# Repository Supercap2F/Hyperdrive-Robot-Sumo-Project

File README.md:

# Hyperdrive-Robot-Sumo-Project
Open Source Robot Sumo Project

* Start Date: Friday, November 28, 2014
*  End Date: ---
*   Version: 1.0

# About
The project started out on November 28th, 2014 - But under a different name: "Epsilon - The Universal Robot".
After more work was done, it was changed to "Hyperdrive!", named after my one of my favorite songs from the band
Guardian. The robot's main function is for Robot sumo, but will also have programs that will allow it to also
be a line flowing robot, and more.

#### Note: You can find photos of the robot in: Hyperdrive-Robot-Sumo-Project/Images/Robot Photos

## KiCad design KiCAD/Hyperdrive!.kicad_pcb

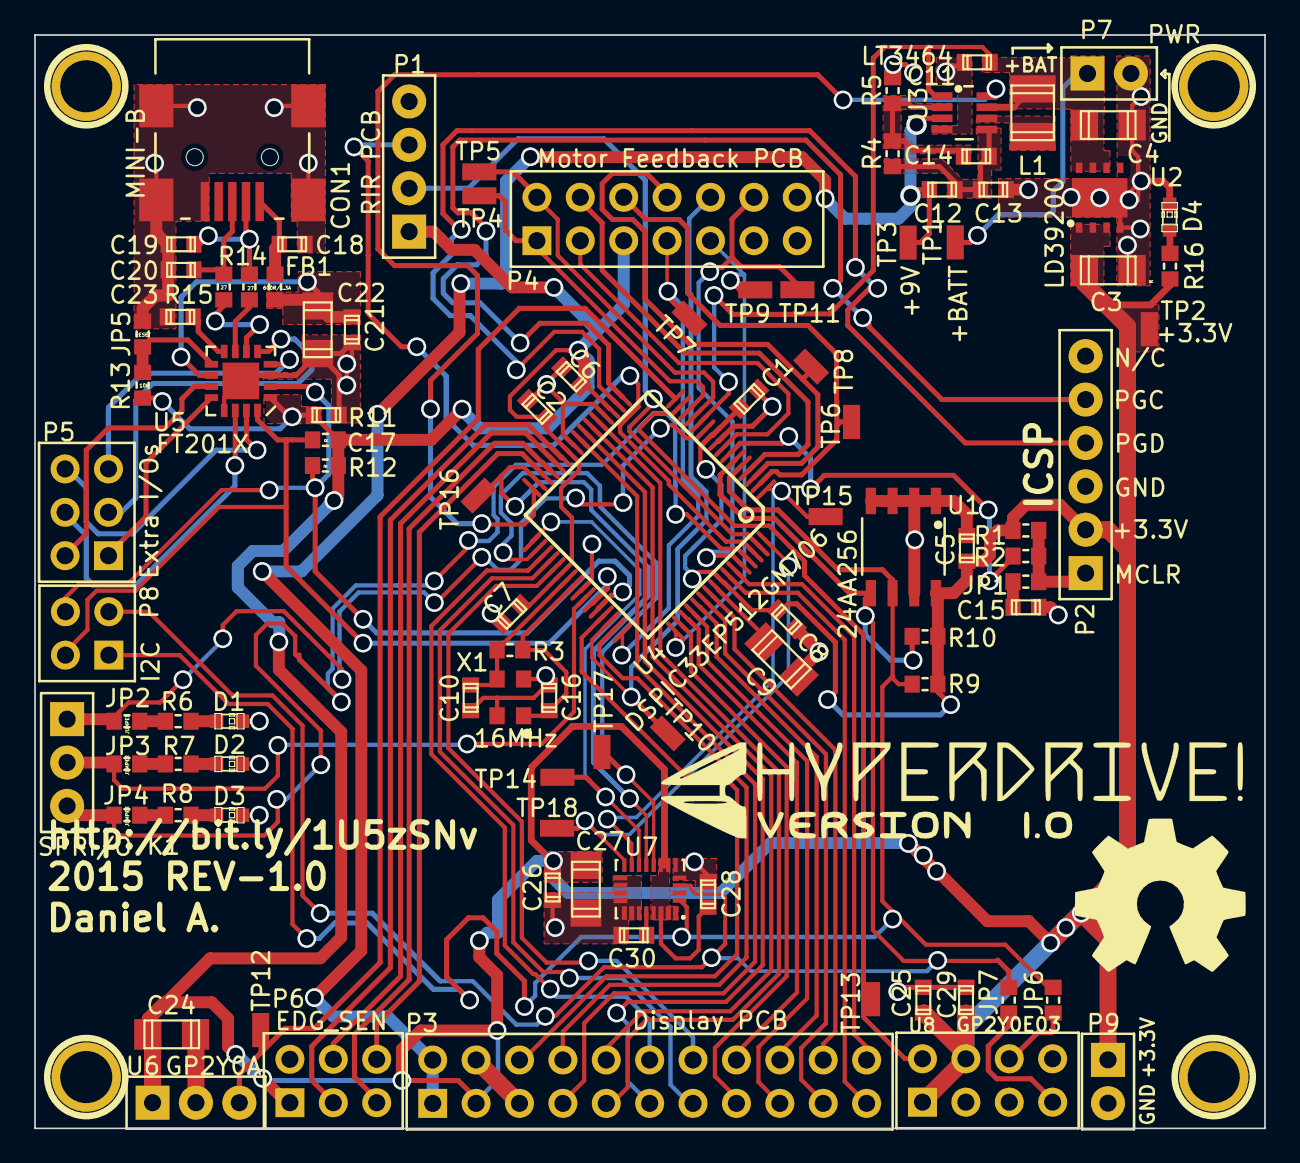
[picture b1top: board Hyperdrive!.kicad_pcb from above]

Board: 2 copper layers, 72.0 x 64.0 mm, 98 parts (0 on the bottom side), 87 nets.

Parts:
C1, C2, C6, C7, C8, C15: 0.1u; c_0603
C3, C4: 10uF; c_1206
C5, C17, C18, C21, C23, C25, C26, C28, C29: 100n; c_0603
C9, C24, C27: 10u; c_1206
C10, C14, C16: 20p; c_0603
C11: 1u; c_0603
C12: 0.47u; c_0603
C13: 2.2u; c_0603
C19, C20: 47p; c_0603
C22: 4.7u; c_1206
C30: 10n; c_0603
CON1: Mini_B
D1, D2, D3, D4: LED-0603
FB1: 600R/1.3A; r_0603
JP1: MCLR; r_0603
JP2, JP3, JP4: JUMPER; r_0603
JP5: RESET; r_0603
JP6: SCL; r_0603
JP7: SDA; r_0603
K1: CON_3x1
L1: 47u; c_1210
P1: CON_4x1
P2: CON_6x1
P3: CON_11x2
P4: CON_7x2
P5, P6: CON_3x2
P7: PWR; CON_2x1
P8: CON_2x2
P9: CON_2x1
R1, R13: 10K; r_0603
R2: 100; r_0603
R3: 1M; r_0603
R4: 1908K; r_0603
R5: 300K; r_0603
R6, R7, R8: 220; r_0603
R9, R10, R11, R12, R16: R; r_0603
R14, R15: 27; r_0603
TP1, TP2, TP3, TP4, TP5, TP6, TP7, TP8, TP9, TP10, TP11, TP12, TP13, TP14, TP15, TP16, TP17, TP18: TP
U1: 24AA256; SOIC_8
U2: LD39200; DFN8
U3: LT3464; TSOT-23
U4: DSPIC33EP512GM706; TQFP_64
U5: FT201X; QFN-16
U6: CON_3x1
U7: LGA-24
U8: CON_4x2
VAL: REF; Hyperdrive!_F.SilkS_40mm
X1: 16MHz; Crystal_2.5x3.2

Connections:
+3.3V: C1.2, C2.1, C3.1, C5.1, C6.2, C7.1, C8.1, C17.1, C24.1, C25.1, C26.1, C27.1, C28.1, C29.1, P1.1, P2.2, P3.3, P4.5, P6.1, P9.1, R1.2, R9.1, R10.1, R11.1, R12.1, R13.1, R16.1, TP2.1, U1.8, U2.1, U2.2, U2.3, U4.10, U4.19, U4.26, U4.38, U4.57, U5.1, U6.1, U7.1, U7.3, U7.7, U7.8, U7.22, U7.23, U7.24, U8.1, U8.4
+9V: C12.1, P3.1, P3.2, TP3.1, U3.3
+BATT: C4.1, C11.1, L1.2, P7.1, TP1.1, U2.6, U2.7, U2.8, U3.1, U3.7, U4.12
/CS#: P3.17, U4.52
/D0: P3.9, U4.21
/D1: P3.10, U4.22
/D2: P3.11, U4.23
/D3: P3.12, U4.35
/D4: P3.13, U4.36
/D5: P3.14, U4.37
/D6: P3.15, U4.50
/D7: P3.16, U4.51
/D/C#: P3.6, U4.45
/DIRL: P4.7, TP7.1, U4.48
/DIRR: P4.10, TP10.1, U4.46
/E/RD#: P3.8, U4.47
/FAULTL: P4.12, TP11.1, U4.60
/FAULTR: P4.9, TP9.1, U4.49
/I/03: JP4.2, K1.3, U4.61
/I/O1: JP2.2, K1.1, U4.11
/I/O2: JP3.2, K1.2, U4.42
/IRBDS: P1.2, U4.63
/IRPWM: P1.3, U4.62
/MCLR: JP1.2, P2.1, R1.1, R2.1
/MSL: P4.1, TP4.1, U4.14
/MSR: P4.2, TP5.1, U4.13
/PGC: P2.5, U4.17
/PGD: P2.4, U4.18
/PWML: P4.8, TP8.1, U4.3
/PWMR: P4.6, TP6.1, U4.2
/R/W#: P3.7, U4.24
/RES#: P3.20, U4.55
/SCL/FM+: P8.3, R11.2, U4.43, U5.16
/SDA/FM+: P8.4, R12.2, U4.44, U5.2
/SHDN: U3.8, U4.32
/ST1: P3.21, U4.58
/ST2: P3.22, U4.59
/ST3: P3.19, U4.54
/ST4: P3.18, U4.53
/Sensors /AD1: P6.3, U4.27
/Sensors /AD2: P6.4, U4.28
/Sensors /AD3: P6.5, U4.29
/Sensors /AD4: P6.6, U4.30
/Sensors /IMU_DEN_G: TP18.1, U4.64, U7.13
/Sensors /IMU_INT1_A: TP14.1, U4.33, U7.11
/Sensors /IMU_INT1_G: TP16.1, U4.31, U7.10
/Sensors /IMU_INT2_A: TP15.1, U4.1, U7.12
/Sensors /IMU_INT2_G: TP17.1, U4.34, U7.9
/Sensors /IMU_SCL: JP6.2, P8.1, R9.2, U1.6, U4.5, U7.2
/Sensors /IMU_SDA: JP7.2, P8.2, R10.2, U1.5, U4.6, U7.4
/Sensors /IRDS_VO: TP12.1, U4.16, U6.3
/Sensors /IRLDS_VO: TP13.1, U4.15, U8.2
/VBUS: C21.1, C22.1, FB1.2, U5.10
/VDD: P4.3, U4.8
/VDD2: P4.4, U4.4
GND: C1.1, C2.2, C3.2, C4.2, C5.2, C6.1, C7.2, C8.2, C9.2, C10.2, C11.2, C13.2, C15.2, C16.2, C17.2, C18.2, C19.2, C20.2, C21.2, C22.2, C23.2, C24.2, C25.2, C26.2, C27.2, C28.2, C29.2, C30.2, CON1.5, CON1.6, CON1.7, CON1.8, CON1.9, D1.2, D2.2, D3.2, D4.2, JP5.2, P1.4, P2.3, P3.4, P3.5, P4.11, P4.13, P4.14, P6.2, P7.2, P9.2, R5.2, U1.1, U1.2, U1.3, U1.4, U1.7, U2.4, U2.9, U3.4, U4.9, U4.20, U4.25, U4.41, U5.3, U5.13, U5.17, U6.2, U7.5, U7.6, U7.14, U7.15, U7.16, U7.17, U7.18, U7.19, U7.20, U8.3, X1.3, X1.4
unnamed: C18.1, CON1.1, FB1.1
unnamed: C19.1, CON1.2, R14.1
unnamed: C20.1, CON1.3, R15.1
unnamed: C15.1, JP1.1
unnamed: JP5.1, R13.2, U5.9
unnamed: C9.1, U4.56
unnamed: C23.1, U5.8
unnamed: R14.2, U5.7
unnamed: R15.2, U5.6
unnamed: JP3.1, R7.1
unnamed: JP4.1, R8.1
unnamed: P5.1, U5.12
unnamed: P5.2, U5.11
unnamed: P5.3, U5.5
unnamed: P5.4, U5.14
unnamed: P5.5, U5.4
unnamed: P5.6, U5.15
unnamed: D1.1, R6.2
unnamed: D2.1, R7.2
unnamed: D3.1, R8.2
unnamed: JP2.1, R6.1
unnamed: R2.2, U4.7
unnamed: C16.1, R3.2, U4.40, X1.1
unnamed: C10.1, R3.1, U4.39, X1.2
unnamed: D4.1, R16.2
unnamed: C12.2, C13.1, C14.1, R4.1, U3.5
unnamed: C14.2, R4.2, R5.1, U3.2
unnamed: L1.1, U3.6
unnamed: JP6.1, U8.6
unnamed: JP7.1, U8.7
unnamed: C30.1, U7.21

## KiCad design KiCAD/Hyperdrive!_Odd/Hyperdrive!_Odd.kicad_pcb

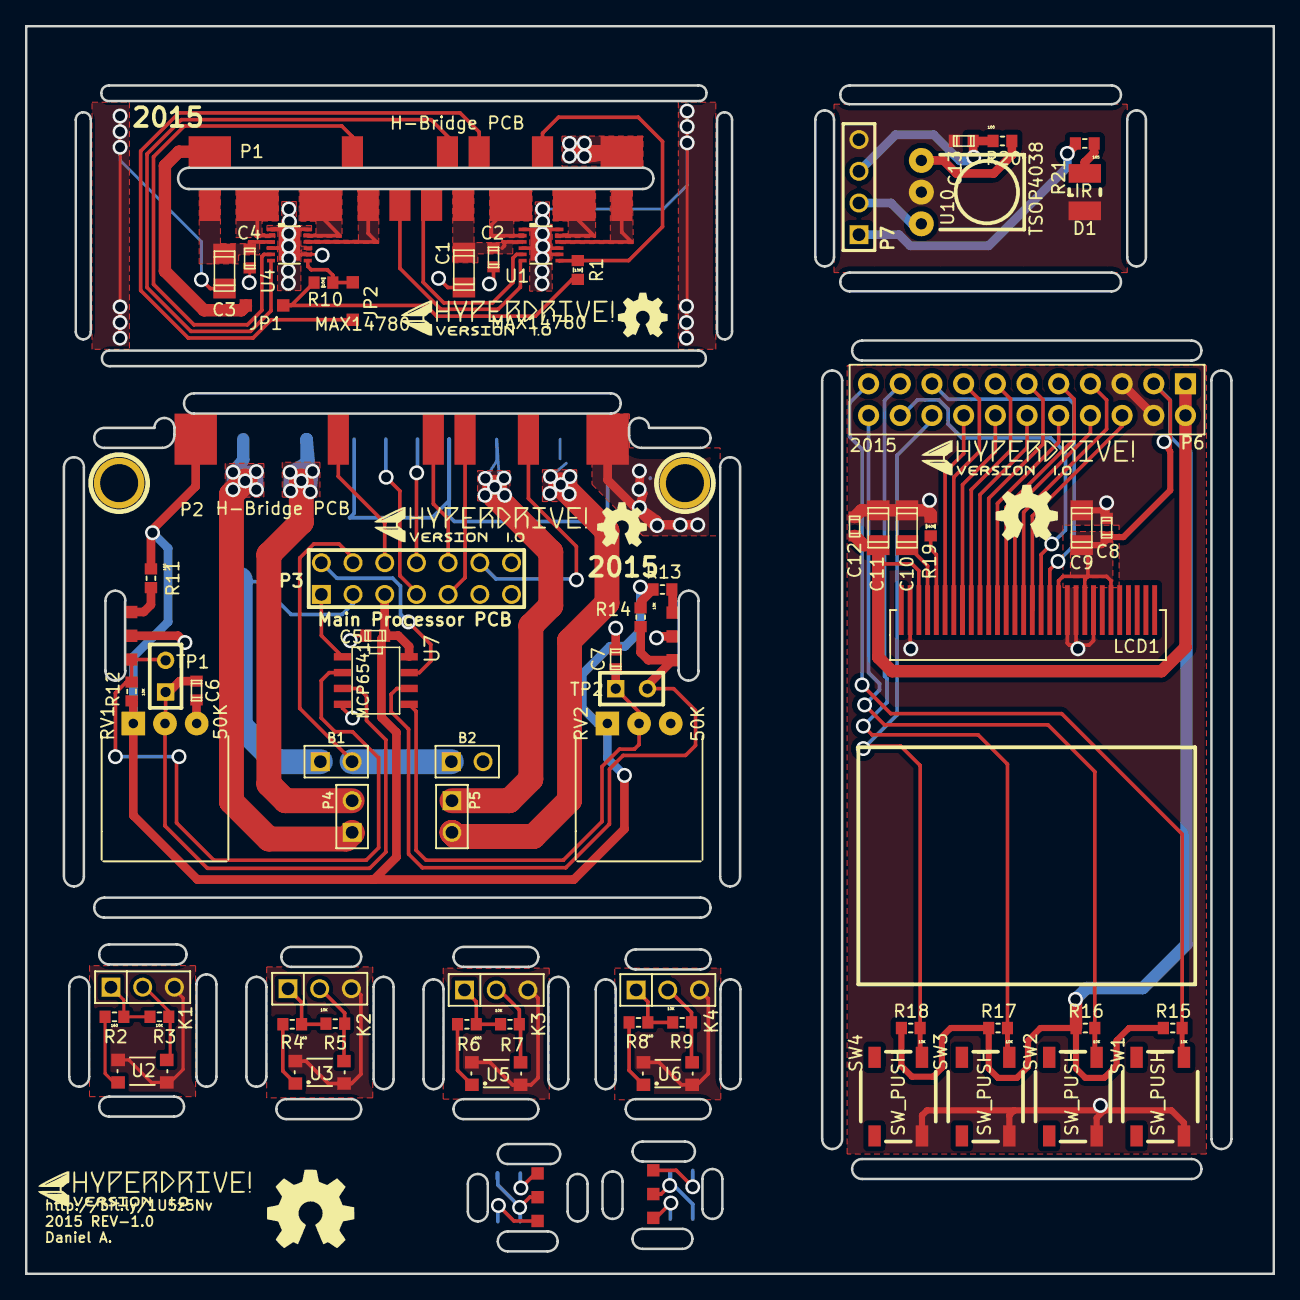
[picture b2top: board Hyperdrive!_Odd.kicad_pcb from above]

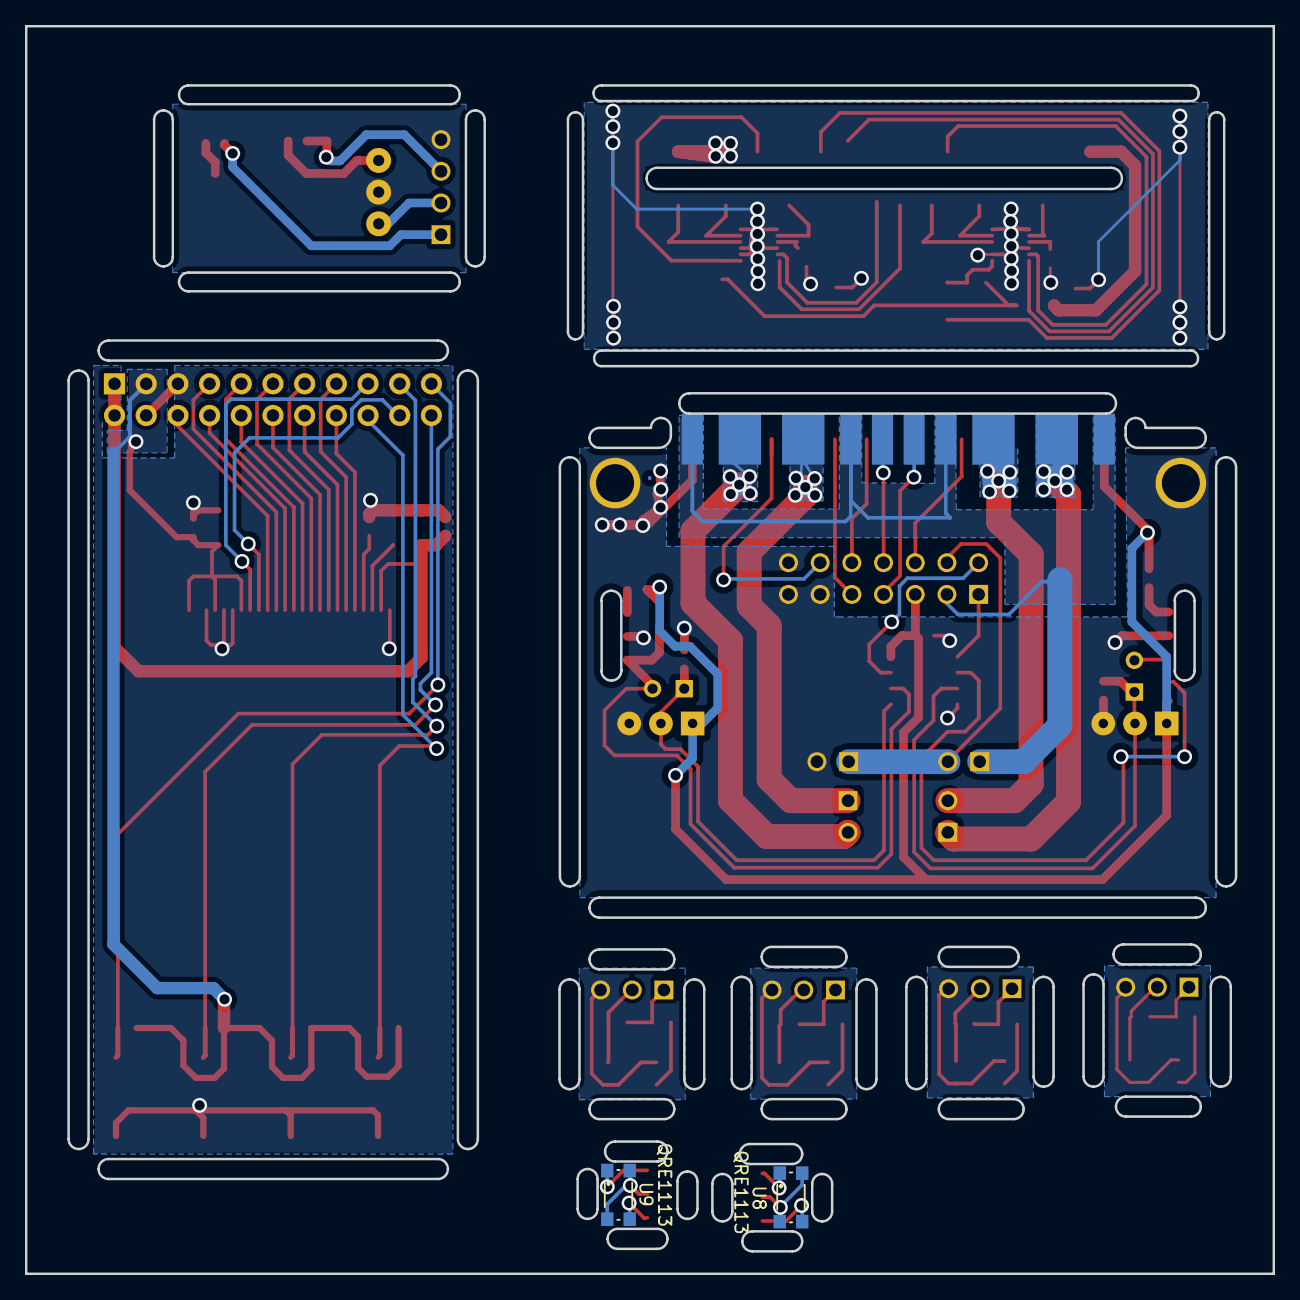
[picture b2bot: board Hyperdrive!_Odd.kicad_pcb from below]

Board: 2 copper layers, 100.0 x 100.0 mm, 70 parts (2 on the bottom side), 79 nets.

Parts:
B1, B2: LiPoly; PIN_ARRAY_2X1
C1, C3: 10u; c_1206
C2, C4: 1u; c_0603
C5: 0.1u; c_0603
C6, C7, C8, C12, C13: 100n; c_0603
C9, C11: 2.2u; c_1206
C10: 4.7u; c_1206
D1: IR; J-Lead
JP1, JP2: Jump_2mm
K1: ES1; PIN_ARRAY_3X1
K2: ES2; PIN_ARRAY_3X1
K3: ES3; PIN_ARRAY_3X1
K4: ES4; PIN_ARRAY_3X1
LCD1: 128X64_LCD; DP
P1: H-Bridge PCB; HR-11
P2: H-Bridge PCB; HR-11-BTB
P3: Main Processor PCB; pin_array_7x2
P4: MR; PIN_ARRAY_2X1
P5: ML; PIN_ARRAY_2X1
P6: CON_11x2
P7: RIR PCB; PIN_ARRAY_4x1
R1, R3, R5, R7, R9, R10, R12, R14, R15, R16, R17, R18: 10K; r_0603
R2, R4, R6, R8, R11, R13: 160; r_0603
R19: 560K; r_0603
R20: 100; r_0603
R21: 165; r_0603
RV1, RV2: 50K; VR
SW1, SW2, SW3, SW4: SW_PUSH; TL3342
TP1, TP2: SIL-2
U1, U4: MAX14780; TDFN
U2, U3, U5, U6: Gull_Wing
U7: MCP6541; SO8E
U8, U9: QRE1113; Gull_Wing
U10: TSOP4038
VAL: REF; Hyperdrive!_F.SilkS_20mm

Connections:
3V3: C5.1, P2.5, P3.5, R11.1, R12.1, R13.1, R14.1, RV1.1, RV2.1, U7.8
+3.3V: JP1.1, JP1.2, P1.5, R1.1, R10.1
+3.3VB: C8.1, C9.1, LCD1.6, LCD1.9, LCD1.12, P6.3, R15.2, R16.2, R17.2, R18.2
+3.3VC: C13.1, P7.3, R20.1
/CS#: LCD1.13, P6.17
/D0: LCD1.18, P6.9
/D1: LCD1.19, P6.10
/D2: LCD1.20, P6.11
/D3: LCD1.21, P6.12
/D4: LCD1.22, P6.13
/D5: LCD1.23, P6.14
/D6: LCD1.24, P6.15
/D7: LCD1.25, P6.16
/D/C#: LCD1.15, P6.6
/DIRL: P1.9, U1.6
/DIRLA: P2.9, P3.7
/DIRR: P1.7, U4.6
/DIRRA: P2.7, P3.10
/E/RD#: LCD1.17, P6.8
/FAULTL: P1.11, R1.2, U1.7
/FAULTLA: P2.11, P3.12
/FAULTR: JP2.1, JP2.2, P1.8, R10.2, U4.7
/FAULTRA: P2.8, P3.9
/IRBDS: P7.2, U10.1
/IRPWM: P7.1, R21.2
/M1L: P1.15, U1.2
/M1LA: P2.15, P5.1
/M1R: P1.13, U4.2
/M1RA: P2.13, P4.1
/M2L: P1.16, U1.11
/M2LA: P2.16, P5.2
/M2R: P1.14, U4.11
/M2RA: P2.14, P4.2
/MSLA: P3.1, U7.1
/MSRA: P3.2, U7.7
/PWML: P1.10, U1.5
/PWMLA: P2.10, P3.8
/PWMR: P1.6, U4.5
/PWMRA: P2.6, P3.6
/R/W#: LCD1.16, P6.7
/RES#: LCD1.14, P6.20
/ST1: P6.21, R15.1, SW1.2
/ST2: P6.22, R16.1, SW2.2
/ST3: P6.19, R17.1, SW3.2
/ST4: P6.18, R18.1, SW4.2
/VDDA: B1.1, P2.1, P2.2, P2.3, P2.4, P3.3
/VDDA2: B1.2, B2.1, P3.4
GND: C1.2, C2.2, C3.2, C4.2, P1.12, U1.1, U1.4, U1.8, U1.9, U1.12, U1.15, U4.1, U4.4, U4.8, U4.9, U4.12, U4.15
GNDA: B2.2, C5.2, C6.2, C7.2, P2.12, P3.11, P3.13, P3.14, RV1.3, RV2.3, U7.4, U8.2, U8.4, U9.2, U9.4
GNDB: C8.2, C9.2, C10.2, C11.2, C12.2, LCD1.8, LCD1.10, LCD1.11, LCD1.29, P6.4, P6.5, R19.2, SW1.1, SW2.1, SW3.1, SW4.1
GNDC: C13.2, D1.1, P7.4, U10.2
unnamed: R13.2, U9.1
unnamed: R14.2, TP2.2, U7.6, U9.3
unnamed: R11.2, U8.1
unnamed: R12.2, TP1.2, U7.2, U8.3
unnamed: K1.2, R3.2, U2.3
unnamed: K3.1, R6.1, R7.1
unnamed: R6.2, U5.1
unnamed: K3.3, U5.2, U5.4
unnamed: K3.2, R7.2, U5.3
unnamed: K1.1, R2.1, R3.1
unnamed: R2.2, U2.1
unnamed: K1.3, U2.2, U2.4
unnamed: K4.3, U6.2, U6.4
unnamed: K4.2, R9.2, U6.3
unnamed: K2.1, R4.1, R5.1
unnamed: R4.2, U3.1
unnamed: K2.3, U3.2, U3.4
unnamed: K2.2, R5.2, U3.3
unnamed: K4.1, R8.1, R9.1
unnamed: R8.2, U6.1
unnamed: D1.2, R21.1
unnamed: C7.1, RV2.2, TP2.1, U7.5
unnamed: C6.1, RV1.2, TP1.1, U7.3
unnamed: R20.2, U10.3
unnamed: LCD1.26, R19.1
unnamed: C10.1, LCD1.27
VCC: C11.1, C12.1, LCD1.28, P6.1, P6.2
VDD: C1.1, C2.1, C3.1, C4.1, P1.1, P1.2, P1.3, P1.4, U1.3, U1.10, U4.3, U4.10

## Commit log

2015-08-04 Added main project files
2015-08-20 Updated ReadMe File
2015-08-25 Updated 3D-Model, and finished main PCB
2015-08-25 Updated README file, and added robot photos.
2015-08-28 Updated 3D-Model, and PCBs.
2015-08-28 Added more photos of the robot
